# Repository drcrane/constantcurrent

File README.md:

A Simple Constant Current Load
==============================

This is a simple implementation of a constant current load that many
in the past have implemented, many are probably better than this one
but a constant current load can bring up lots of interesting issues
and OpAmp stability is one of them.

This work is not novel or unique and as such I cannot claim any
originality, it is just an implementation of something many have
done before me. Please use it as you wish.

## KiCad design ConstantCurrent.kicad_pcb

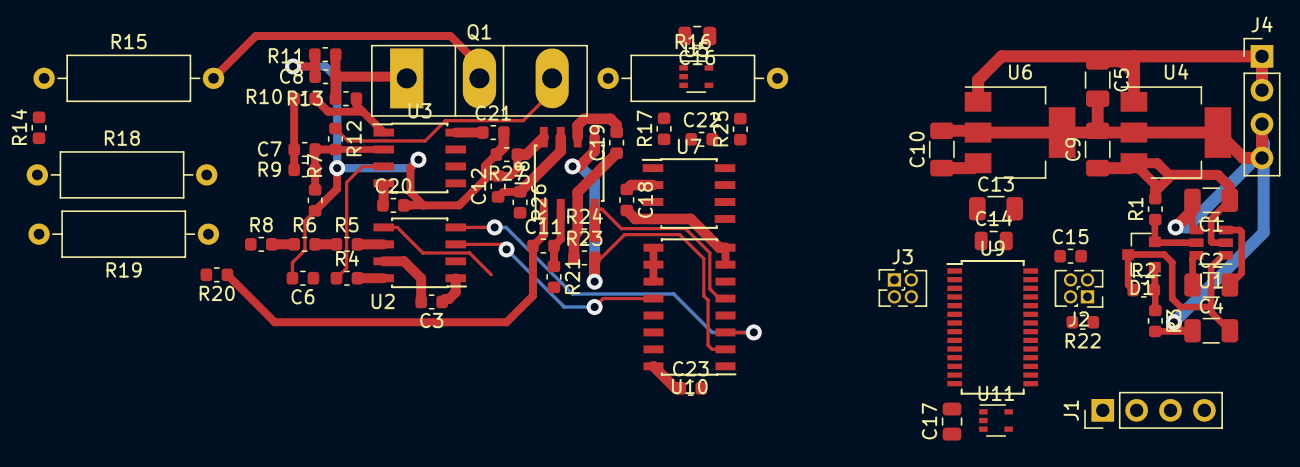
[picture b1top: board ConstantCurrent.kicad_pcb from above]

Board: 2 copper layers, 67 parts (0 on the bottom side), 45 nets.

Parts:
C1, C2: CP1; C_1206_3216Metric
C3, C6, C11, C12, C18, C19, C20, C21, C22: C; C_0603_1608Metric
C4, C5, C9, C10, C13: 10uF; C_1206_3216Metric
C7, C15: 10nF; C_0603_1608Metric
C8, C23: 100nF; C_0603_1608Metric
C14, C16, C17: 1uF; C_0805_2012Metric
D1: TL432DBZ; SOT-23
J1, J4: Conn_01x04; PinHeader_1x04_P2.54mm_Vertical
J2, J3: Conn_01x04; PinHeader_2x02_P1.27mm_Vertical
Q1: Q_NMOS_GDS; TO-247-3_Vertical
R1, R2, R3, R17, R20, R21, R25, R26, R27: R; R_0603_1608Metric
R4, R8: 500R; R_0603_1608Metric
R5: 6k8; R_0603_1608Metric
R6: 2k2; R_0603_1608Metric
R7: 0R; R_0603_1608Metric
R9, R13: 470; R_0603_1608Metric
R10, R14: 0; R_0603_1608Metric
R11: 5k; R_0603_1608Metric
R12: 1k; R_0603_1608Metric
R15: 56; R_Axial_DIN0309_L9.0mm_D3.2mm_P12.70mm_Horizontal
R16: 10; R_Axial_DIN0309_L9.0mm_D3.2mm_P12.70mm_Horizontal
R18, R19: R; R_Axial_DIN0309_L9.0mm_D3.2mm_P12.70mm_Horizontal
R22: 10k; R_0603_1608Metric
R23, R24: 4k7; R_0603_1608Metric
U1: NCP1729; SOT-23-6
U2: MCP4822; SOIC-8_3.9x4.9mm_P1.27mm
U3: OPA2227_SO8; SOIC-8_3.9x4.9mm_P1.27mm
U4: MCP1703A-5002_SOT223; SOT-223-3_TabPin2
U5, U11: LMT86DCK; SOT-353_SC-70-5
U6: MCP1703A-3302_SOT223; SOT-223-3_TabPin2
U7: MAX4080S; SOIC-8_3.9x4.9mm_P1.27mm
U8: MCP3422; SOIC-8_3.9x4.9mm_P1.27mm
U9: MSP430G2553IPW28; TSSOP-28_4.4x9.7mm_P0.65mm
U10: CD4053B; SOIC-16_3.9x9.9mm_P1.27mm

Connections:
3V3: C3.1, C10.1, C13.1, C14.1, C18.1, C19.1, C23.1, J2.1, J3.1, R22.1, R23.1, R24.1, U2.1, U5.4, U5.5, U6.3, U7.2, U8.3, U9.1, U10.16, U11.4, U11.5
5V: C1.1, C9.1, C21.1, J1.2, R1.2, U1.2, U3.8, U4.3
12V: C5.1, J4.1, J4.2, R14.1, R18.1, U4.1, U6.1
GND: C1.2, C3.2, C4.1, C5.2, C6.2, C8.2, C9.2, C10.2, C13.2, C14.2, C15.2, C16.2, C17.2, C18.2, C19.2, C20.2, C21.2, C23.2, J1.1, J2.4, J3.4, J4.3, J4.4, R3.2, R7.2, R11.2, R16.2, R19.2, R21.2, R25.2, R27.2, U1.4, U2.7, U4.2, U5.1, U5.2, U6.2, U7.4, U8.6, U9.28, U10.7, U10.8, U11.1, U11.2
LMT_BOARD: C17.1, U9.5, U11.3
LMT_SHUNT: C16.1, U5.3, U9.6
MSP430_TEST: J2.3, U9.25
NEG_V1: C4.2, C20.1, D1.3, R2.1, U1.1, U3.4
unnamed: C2.1, U1.6
unnamed: C2.2, U1.3
unnamed: C6.1, R4.1, R8.1, U3.3
unnamed: C7.1, R9.1, R10.1
unnamed: C7.2, R7.1, R9.2, R12.2, U3.2
unnamed: C8.1, Q1.1, R11.1, R13.1
unnamed: C11.1, R20.1, U8.1
unnamed: C11.2, R21.1, U8.2
unnamed: C12.1, R26.1, U8.7
unnamed: C12.2, R27.1, U8.8
unnamed: C22.1, R17.1, U7.1
unnamed: C22.2, R25.1, U7.8
unnamed: D1.1, R2.2, R3.1
unnamed: D1.2, R1.1, U1.5
unnamed: Q1.2, R15.2
unnamed: Q1.3, R12.1, R16.1, R17.2
unnamed: R4.2, U2.8
unnamed: R5.1, R6.2
unnamed: R5.2, U2.6
unnamed: R6.1, R8.2
unnamed: R10.2, R13.2, U3.1
unnamed: R14.2, R15.1
unnamed: R18.2, R19.1, R20.2
unnamed: R26.2, U7.5
unnamed: U9.23, U10.4
unnamed: U9.11, U10.6
unnamed: U9.10, U10.9, U10.10, U10.11
unnamed: U9.22, U10.14
unnamed: U9.7, U10.15
UCA0RXD: J3.2, U9.3
UCA0TXD: J3.3, U9.4
UCB0CLK: U2.3, U10.12, U10.13
UCB0SCL: J1.3, R23.2, U8.5, U10.2
UCB0SDA: J1.4, R24.2, U8.4, U10.5
UCB0SIMO: U2.4, U10.3
~LDAC: U2.5, U9.12
~MSP430_RST: C15.1, J2.2, R22.2, U9.24
